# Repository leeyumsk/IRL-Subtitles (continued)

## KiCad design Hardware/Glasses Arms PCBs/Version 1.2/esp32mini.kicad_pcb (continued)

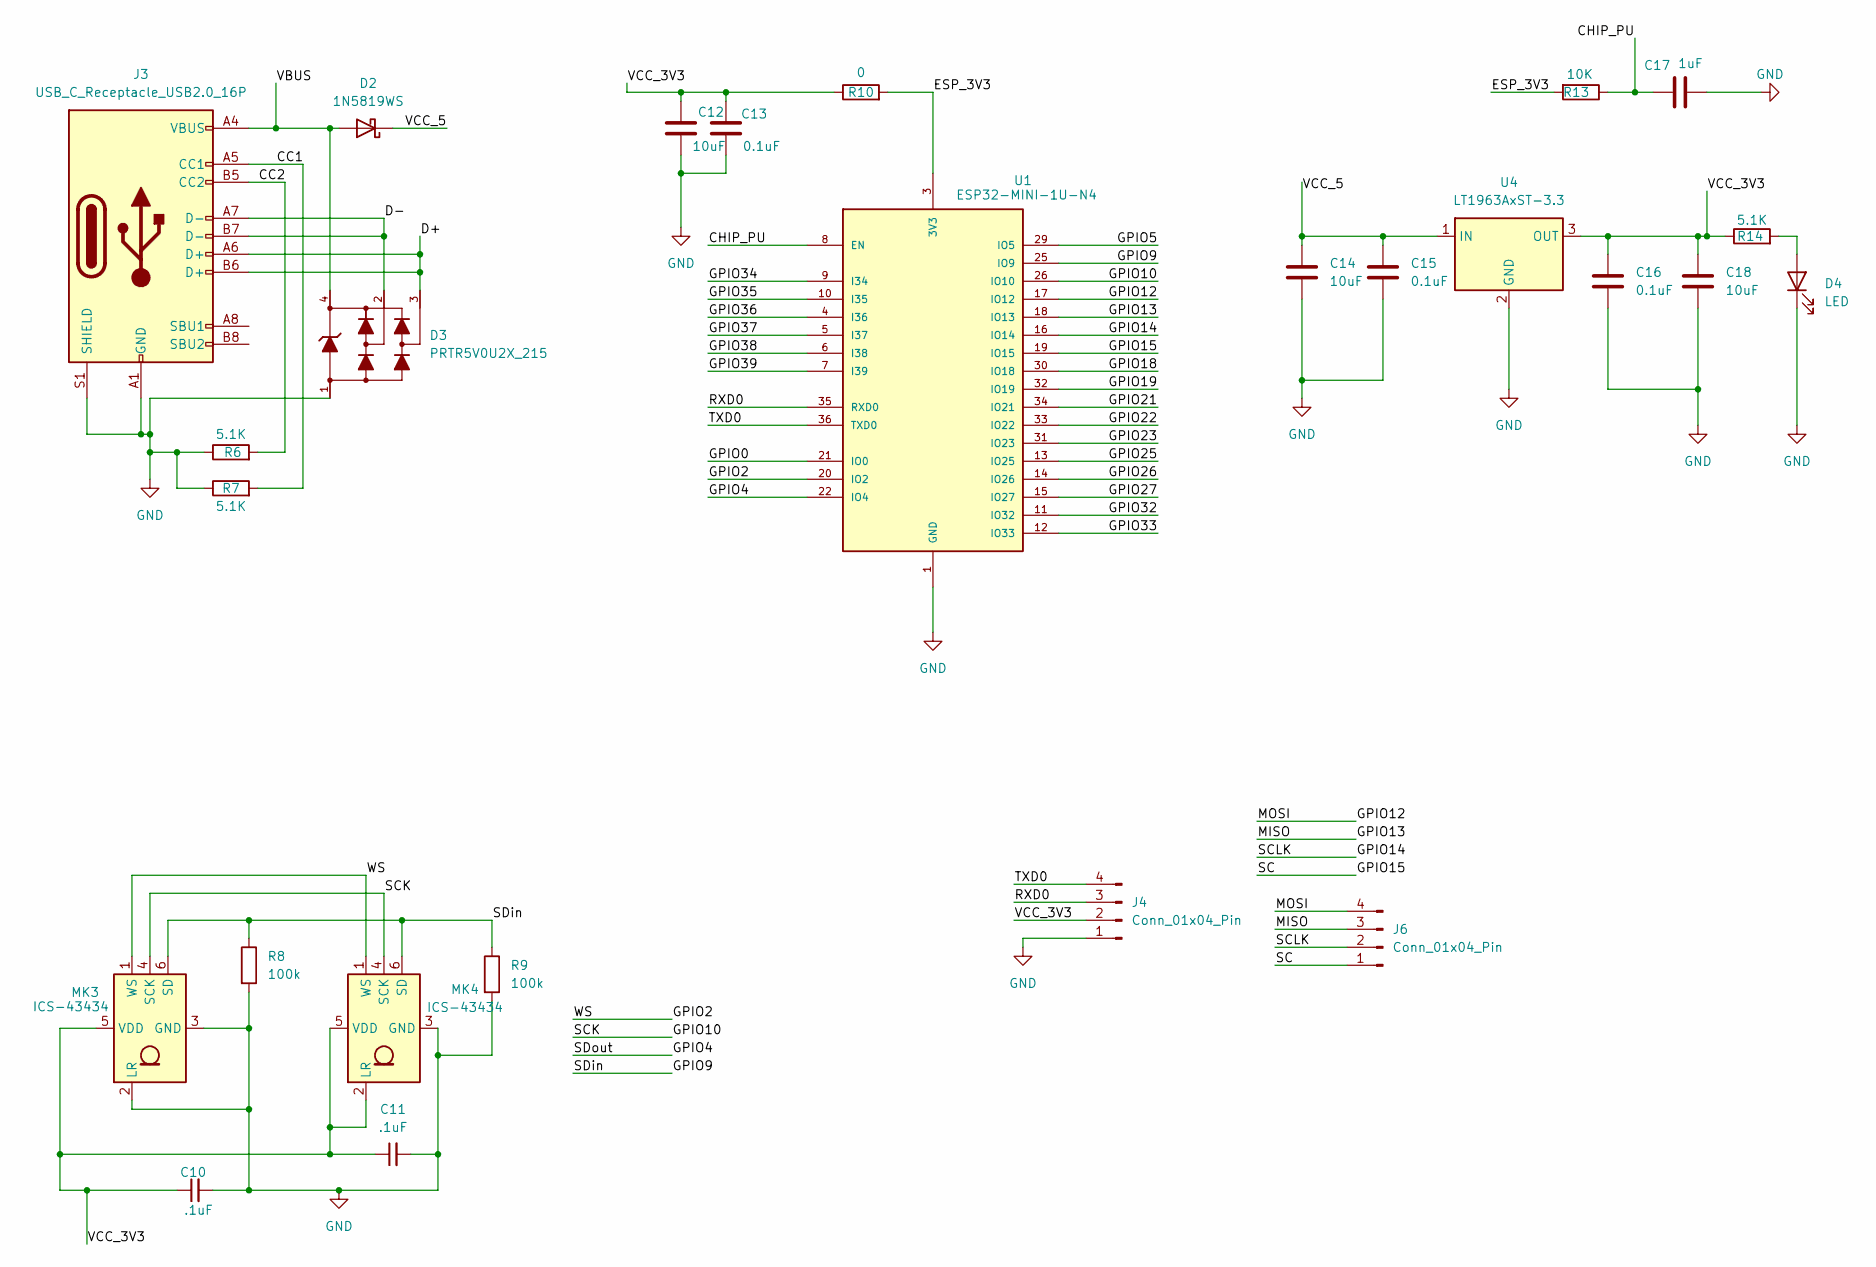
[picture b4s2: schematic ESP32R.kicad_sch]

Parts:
C10, C11: .1uF; C_0805_2012Metric_Pad1.18x1.45mm_HandSolder
C12, C14, C18: 10uF; C_0805_2012Metric_Pad1.18x1.45mm_HandSolder
C13, C15, C16: 0.1uF; C_0805_2012Metric_Pad1.18x1.45mm_HandSolder
C17: 1uF; C_0805_2012Metric_Pad1.18x1.45mm_HandSolder
D2: 1N5819WS; D_SOD-323
D3: PRTR5V0U2X_215; SOT143B
D4: LED; LED_0603_1608Metric_Pad1.05x0.95mm_HandSolder
J3: USB_C_Receptacle_USB2.0_16P; USB_C_Receptacle_JAE_DX07S016JA1R1500
J4, J6: Conn_01x04_Pin; PinHeader_1x04_P1.27mm_Vertical
MK3, MK4: ICS-43434; InvenSense_ICS-43434-6_3.5x2.65mm
R6, R7: 5.1K; R_0805_2012Metric_Pad1.20x1.40mm_HandSolder
R8, R9: 100k; R_0805_2012Metric_Pad1.20x1.40mm_HandSolder
R10: 0; SolderJumper-2_P1.3mm_Open_RoundedPad1.0x1.5mm
R13: 10K; R_0805_2012Metric
R14: 5.1K; R_0603_1608Metric_Pad0.98x0.95mm_HandSolder
U1: ESP32-MINI-1U-N4; MODULE_ESP32-MINI-1U-N4; PARTREV v1.2
U4: LT1963AxST-3.3; DCY0004A_N

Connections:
/BoardR/CC1: J3.A5 (CC1), R7.2
/BoardR/CC2: J3.B5 (CC2), R6.2
/BoardR/CHIP_PU: C17.1, R13.1, U1.8 (EN)
/BoardR/D+: D3.3, J3.A6 (D+), J3.B6 (D+)
/BoardR/D-: D3.2, J3.A7 (D-), J3.B7 (D-)
/BoardR/ESP_3V3: R10.2, R13.2, U1.3 (3V3)
/BoardR/GPIO0: U1.21 (IO0)
/BoardR/GPIO2: MK3.1 (WS), MK4.1 (WS), U1.20 (IO2)
/BoardR/GPIO4: U1.22 (IO4)
/BoardR/GPIO5: U1.29 (IO5)
/BoardR/GPIO9: MK3.6 (SD), MK4.6 (SD), R8.1, R9.1, U1.25 (IO9)
/BoardR/GPIO10: MK3.4 (SCK), MK4.4 (SCK), U1.26 (IO10)
/BoardR/GPIO12: J6.4, U1.17 (IO12)
/BoardR/GPIO13: J6.3, U1.18 (IO13)
/BoardR/GPIO14: J6.2, U1.16 (IO14)
/BoardR/GPIO15: J6.1, U1.19 (IO15)
/BoardR/GPIO18: U1.30 (IO18)
/BoardR/GPIO19: U1.32 (IO19)
/BoardR/GPIO21: U1.34 (IO21)
/BoardR/GPIO22: U1.33 (IO22)
/BoardR/GPIO23: U1.31 (IO23)
/BoardR/GPIO25: U1.13 (IO25)
/BoardR/GPIO26: U1.14 (IO26)
/BoardR/GPIO27: U1.15 (IO27)
/BoardR/GPIO32: U1.11 (IO32)
/BoardR/GPIO33: U1.12 (IO33)
/BoardR/GPIO34: U1.9 (I34)
/BoardR/GPIO35: U1.10 (I35)
/BoardR/GPIO36: U1.4 (I36)
/BoardR/GPIO37: U1.5 (I37)
/BoardR/GPIO38: U1.6 (I38)
/BoardR/GPIO39: U1.7 (I39)
/BoardR/RXD0: J4.3, U1.35 (RXD0)
/BoardR/TXD0: J4.4, U1.36 (TXD0)
/BoardR/VBUS: D2.2 (A), D3.4, J3.A4 (VBUS), J3.A9 (VBUS), J3.B4 (VBUS), J3.B9 (VBUS)
/BoardR/VCC_3V3: C10.1, C11.1, C12.1, C13.1, C16.1, C18.1, J4.2, MK3.5 (VDD), MK4.2 (LR), MK4.5 (VDD), R10.1, R14.1, U4.3 (OUT)
/BoardR/VCC_5: C14.1, C15.1, D2.1 (K), U4.1 (IN)
GND: C10.2, C11.2, C12.2, C13.2, C14.2, C15.2, C16.2, C17.2, C18.2, D3.1, D4.1 (K), J3.A1 (GND), J3.A12 (GND), J3.B1 (GND), J3.B12 (GND), J3.S1 (SHIELD), J4.1, MK3.2 (LR), MK3.3 (GND), MK4.3 (GND), R6.1, R7.1, R8.2, R9.2, U1.1 (GND), U1.2 (GND), U1.27 (GND), U1.38 (GND), U1.39 (GND), U1.40 (GND), U1.41 (GND), U1.42 (GND), U1.43 (GND), U1.44 (GND), U1.45 (GND), U1.46 (GND), U1.47 (GND), U1.48 (GND), U1.49 (GND), U1.50 (GND), U1.51 (GND), U1.52 (GND), U1.53 (GND), U1.54 (GND), U1.55 (GND), U1.56 (GND), U1.57 (GND), U1.58 (GND), U1.59 (GND), U1.60 (GND), U1.61 (GND), U1.62 (GND), U4.2 (GND); also elsewhere on the board
unnamed: D4.2 (A), R14.2

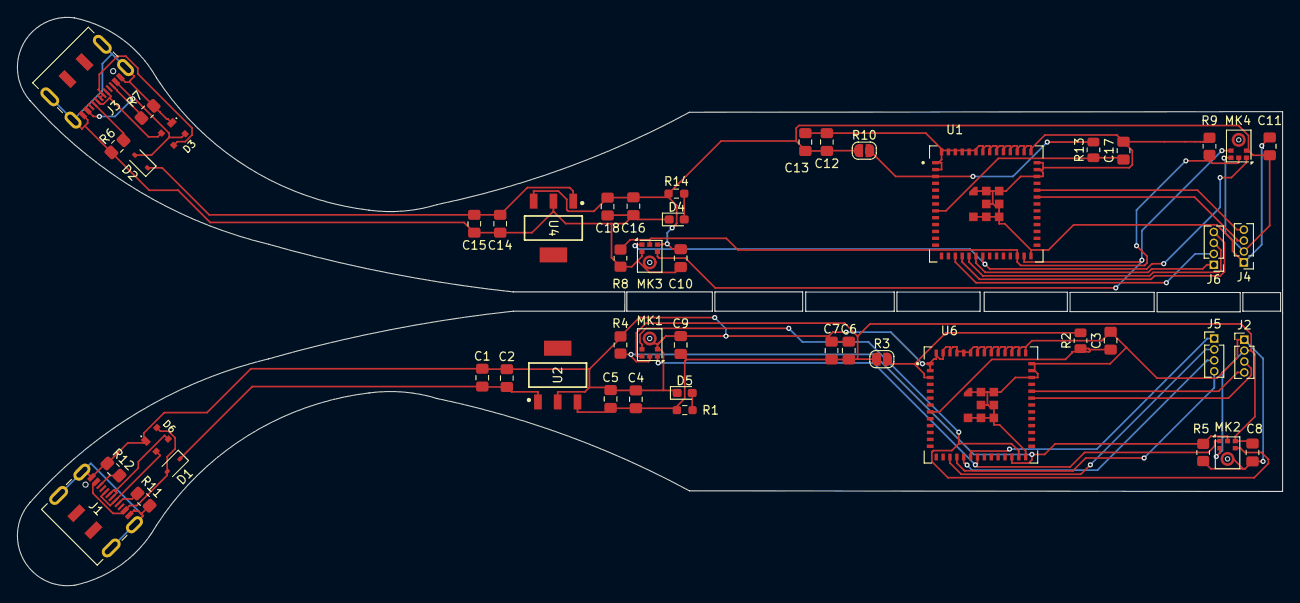
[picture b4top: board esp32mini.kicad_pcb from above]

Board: 2 copper layers, 147.1 x 66.1 mm, 52 parts (0 on the bottom side), 39 nets.

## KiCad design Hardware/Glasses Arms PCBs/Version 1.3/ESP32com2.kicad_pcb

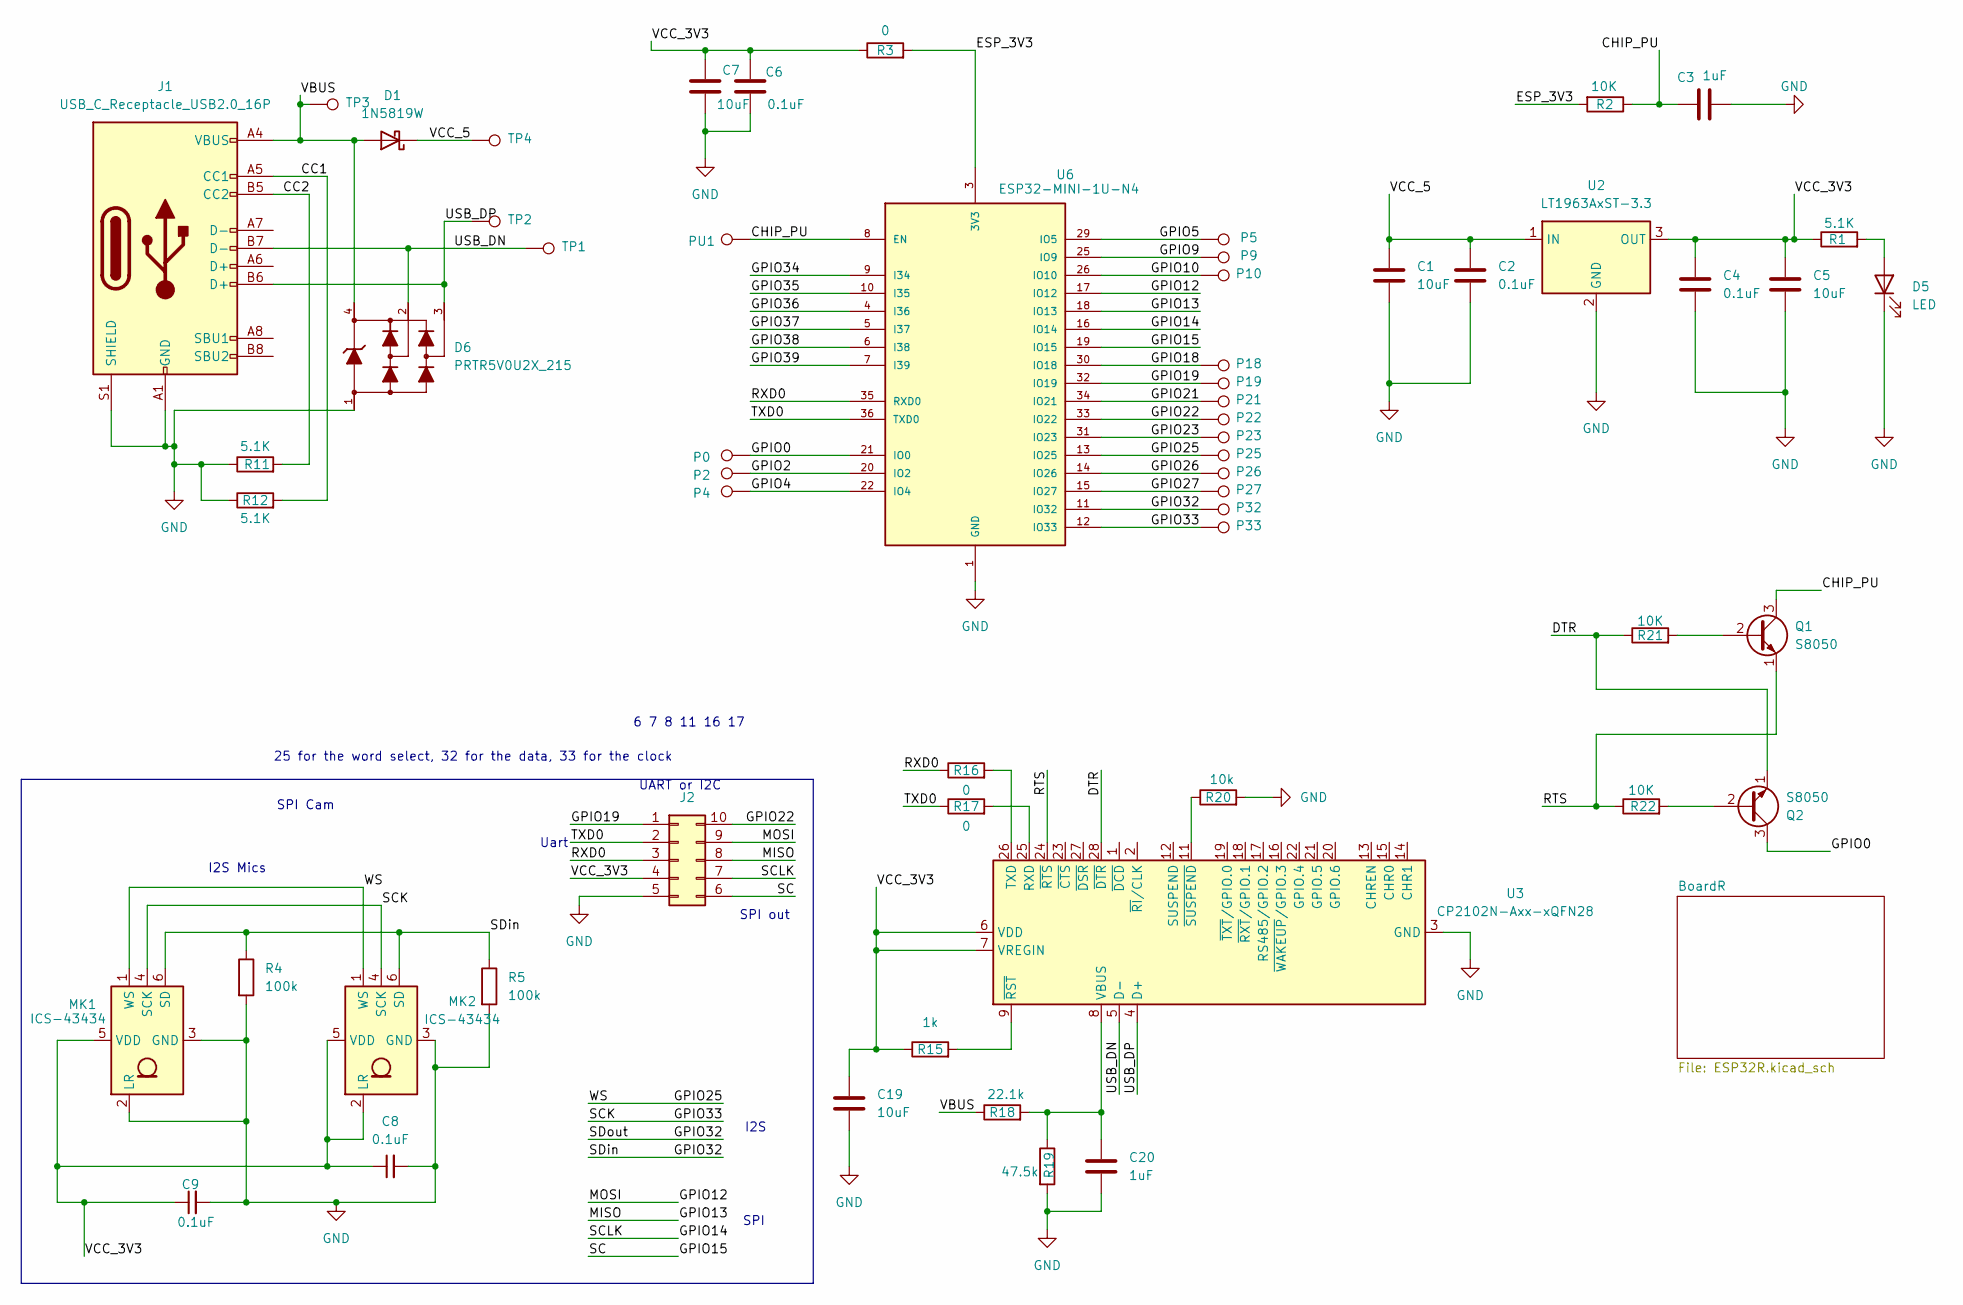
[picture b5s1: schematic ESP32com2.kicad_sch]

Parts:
C1, C5, C7, C19: 10uF; C_0805_2012Metric_Pad1.18x1.45mm_HandSolder
C2, C4, C6, C8, C9: 0.1uF; C_0805_2012Metric_Pad1.18x1.45mm_HandSolder
C3, C20: 1uF; C_0805_2012Metric_Pad1.18x1.45mm_HandSolder
D1: 1N5819W; D_SOD-123F
D5: LED; LED_0603_1608Metric_Pad1.05x0.95mm_HandSolder
D6: PRTR5V0U2X_215; SOT143B
J1: USB_C_Receptacle_USB2.0_16P; USB_C_Receptacle_JAE_DX07S016JA1R1500
J2: Conn_02x04_Counter_Clockwise; PinSocket_2x05_P2.00mm_Vertical
MK1, MK2: ICS-43434; InvenSense_ICS-43434-6_3.5x2.65mm
P0, P2, P4, P5, P9, P10, P18, P19, P21, P22, P23, P25, P26, P27, P32, P33: TestPoint; TestPoint_Pad_1.0x1.0mm
PU1: TestPoint; TestPoint_Pad_1.0x1.0mm
Q1, Q2: S8050; SOT-23-3
R1: 5.1K; R_0603_1608Metric_Pad0.98x0.95mm_HandSolder
R2: 10K; R_0805_2012Metric
R3: 0; SolderJumper-2_P1.3mm_Open_RoundedPad1.0x1.5mm
R4, R5: 100k; R_0805_2012Metric_Pad1.20x1.40mm_HandSolder
R11, R12: 5.1K; R_0805_2012Metric_Pad1.20x1.40mm_HandSolder
R15: 1k; R_0805_2012Metric_Pad1.20x1.40mm_HandSolder
R16, R17: 0; SolderJumper-2_P1.3mm_Bridged_RoundedPad1.0x1.5mm
R18: 22.1k; R_0805_2012Metric_Pad1.20x1.40mm_HandSolder
R19: 47.5k; R_0805_2012Metric_Pad1.20x1.40mm_HandSolder
R20: 10k; R_0805_2012Metric_Pad1.20x1.40mm_HandSolder
R21, R22: 10K; R_0805_2012Metric_Pad1.20x1.40mm_HandSolder
TP1, TP2, TP3, TP4: TestPoint; TestPoint_Pad_1.0x1.0mm
U2: LT1963AxST-3.3; SOT-223-3_TabPin2
U3: CP2102N-Axx-xQFN28; QFN-28-1EP_5x5mm_P0.5mm_EP3.35x3.35mm
U6: ESP32-MINI-1U-N4; MODULE_ESP32-MINI-1U-N4; PARTREV v1.2

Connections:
/CC1: J1.A5 (CC1), R12.2
/CC2: J1.B5 (CC2), R11.2
/CHIP_PU: C3.1, PU1.1, Q1.3 (C), R2.1, U6.8 (EN)
/DTR: Q2.1 (E), R21.1, U3.28 (~DTR)
/ESP_3V3: R2.2, R3.2, U6.3 (3V3)
/GPIO0: P0.1, Q2.3 (C), U6.21 (IO0)
/GPIO2: P2.1, U6.20 (IO2)
/GPIO4: P4.1, U6.22 (IO4)
/GPIO5: P5.1, U6.29 (IO5)
/GPIO9: P9.1, U6.25 (IO9)
/GPIO10: P10.1, U6.26 (IO10)
/GPIO12: J2.9, U6.17 (IO12)
/GPIO13: J2.8, U6.18 (IO13)
/GPIO14: J2.7, U6.16 (IO14)
/GPIO15: J2.6, U6.19 (IO15)
/GPIO18: P18.1, U6.30 (IO18)
/GPIO19: J2.1, P19.1, U6.32 (IO19)
/GPIO21: P21.1, U6.34 (IO21)
/GPIO22: J2.10, P22.1, U6.33 (IO22)
/GPIO23: P23.1, U6.31 (IO23)
/GPIO25: MK1.1 (WS), MK2.1 (WS), P25.1, U6.13 (IO25)
/GPIO26: P26.1, U6.14 (IO26)
/GPIO27: P27.1, U6.15 (IO27)
/GPIO32: MK1.6 (SD), MK2.6 (SD), P32.1, R4.1, R5.1, U6.11 (IO32)
/GPIO33: MK1.4 (SCK), MK2.4 (SCK), P33.1, U6.12 (IO33)
/GPIO34: U6.9 (I34)
/GPIO35: U6.10 (I35)
/GPIO36: U6.4 (I36)
/GPIO37: U6.5 (I37)
/GPIO38: U6.6 (I38)
/GPIO39: U6.7 (I39)
/RTS: Q1.1 (E), R22.1, U3.24 (~RTS)
/RXD0: J2.3, R16.1, U6.35 (RXD0)
/TXD0: J2.2, R17.1, U6.36 (TXD0)
/USB_DN: D6.2, J1.B7 (D-), TP1.1, U3.5 (D-)
/USB_DP: D6.3, J1.B6 (D+), TP2.1, U3.4 (D+)
/VBUS: D1.2 (A), D6.4, J1.A4 (VBUS), J1.A9 (VBUS), J1.B4 (VBUS), J1.B9 (VBUS), R18.1, TP3.1
/VCC_3V3: C4.1, C5.1, C6.1, C7.1, C8.1, C9.1, C19.1, J2.4, MK1.5 (VDD), MK2.2 (LR), MK2.5 (VDD), R1.1, R3.1, R15.1, U2.3 (OUT), U3.6 (VDD), U3.7 (VREGIN)
/VCC_5: C1.1, C2.1, D1.1 (K), TP4.1, U2.1 (IN)
GND: C1.2, C2.2, C3.2, C4.2, C5.2, C6.2, C7.2, C8.2, C9.2, C19.2, C20.2, D5.1 (K), D6.1, J1.A1 (GND), J1.A12 (GND), J1.B1 (GND), J1.B12 (GND), J1.S1 (SHIELD), J2.5, MK1.2 (LR), MK1.3 (GND), MK2.3 (GND), R4.2, R5.2, R11.1, R12.1, R19.2, R20.2, U2.2 (GND), U2.4 (GND), U3.3 (GND), U3.29 (GND), U6.1 (GND), U6.2 (GND), U6.27 (GND), U6.38 (GND), U6.39 (GND), U6.40 (GND), U6.41 (GND), U6.42 (GND), U6.43 (GND), U6.44 (GND), U6.45 (GND), U6.46 (GND), U6.47 (GND), U6.48 (GND), U6.49 (GND), U6.50 (GND), U6.51 (GND), U6.52 (GND), U6.53 (GND), U6.54 (GND), U6.55 (GND), U6.56 (GND), U6.57 (GND), U6.58 (GND), U6.59 (GND), U6.60 (GND), U6.61 (GND), U6.62 (GND); also elsewhere on the board
unnamed: D5.2 (A), R1.2
unnamed: Q1.2 (B), R21.2
unnamed: Q2.2 (B), R22.2
unnamed: R17.2, U3.25 (RXD)
unnamed: R16.2, U3.26 (TXD)
unnamed: C20.1, R18.2, R19.1, U3.8 (VBUS)
unnamed: R15.2, U3.9 (~RST)
unnamed: R20.1, U3.11 (~SUSPEND)

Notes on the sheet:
UART or I2C
I2S
SPI Cam
25 for the word select, 32 for the data, 33 for the clock
I2S Mics
Uart
SPI out
6 7 8 11 16 17
SPI

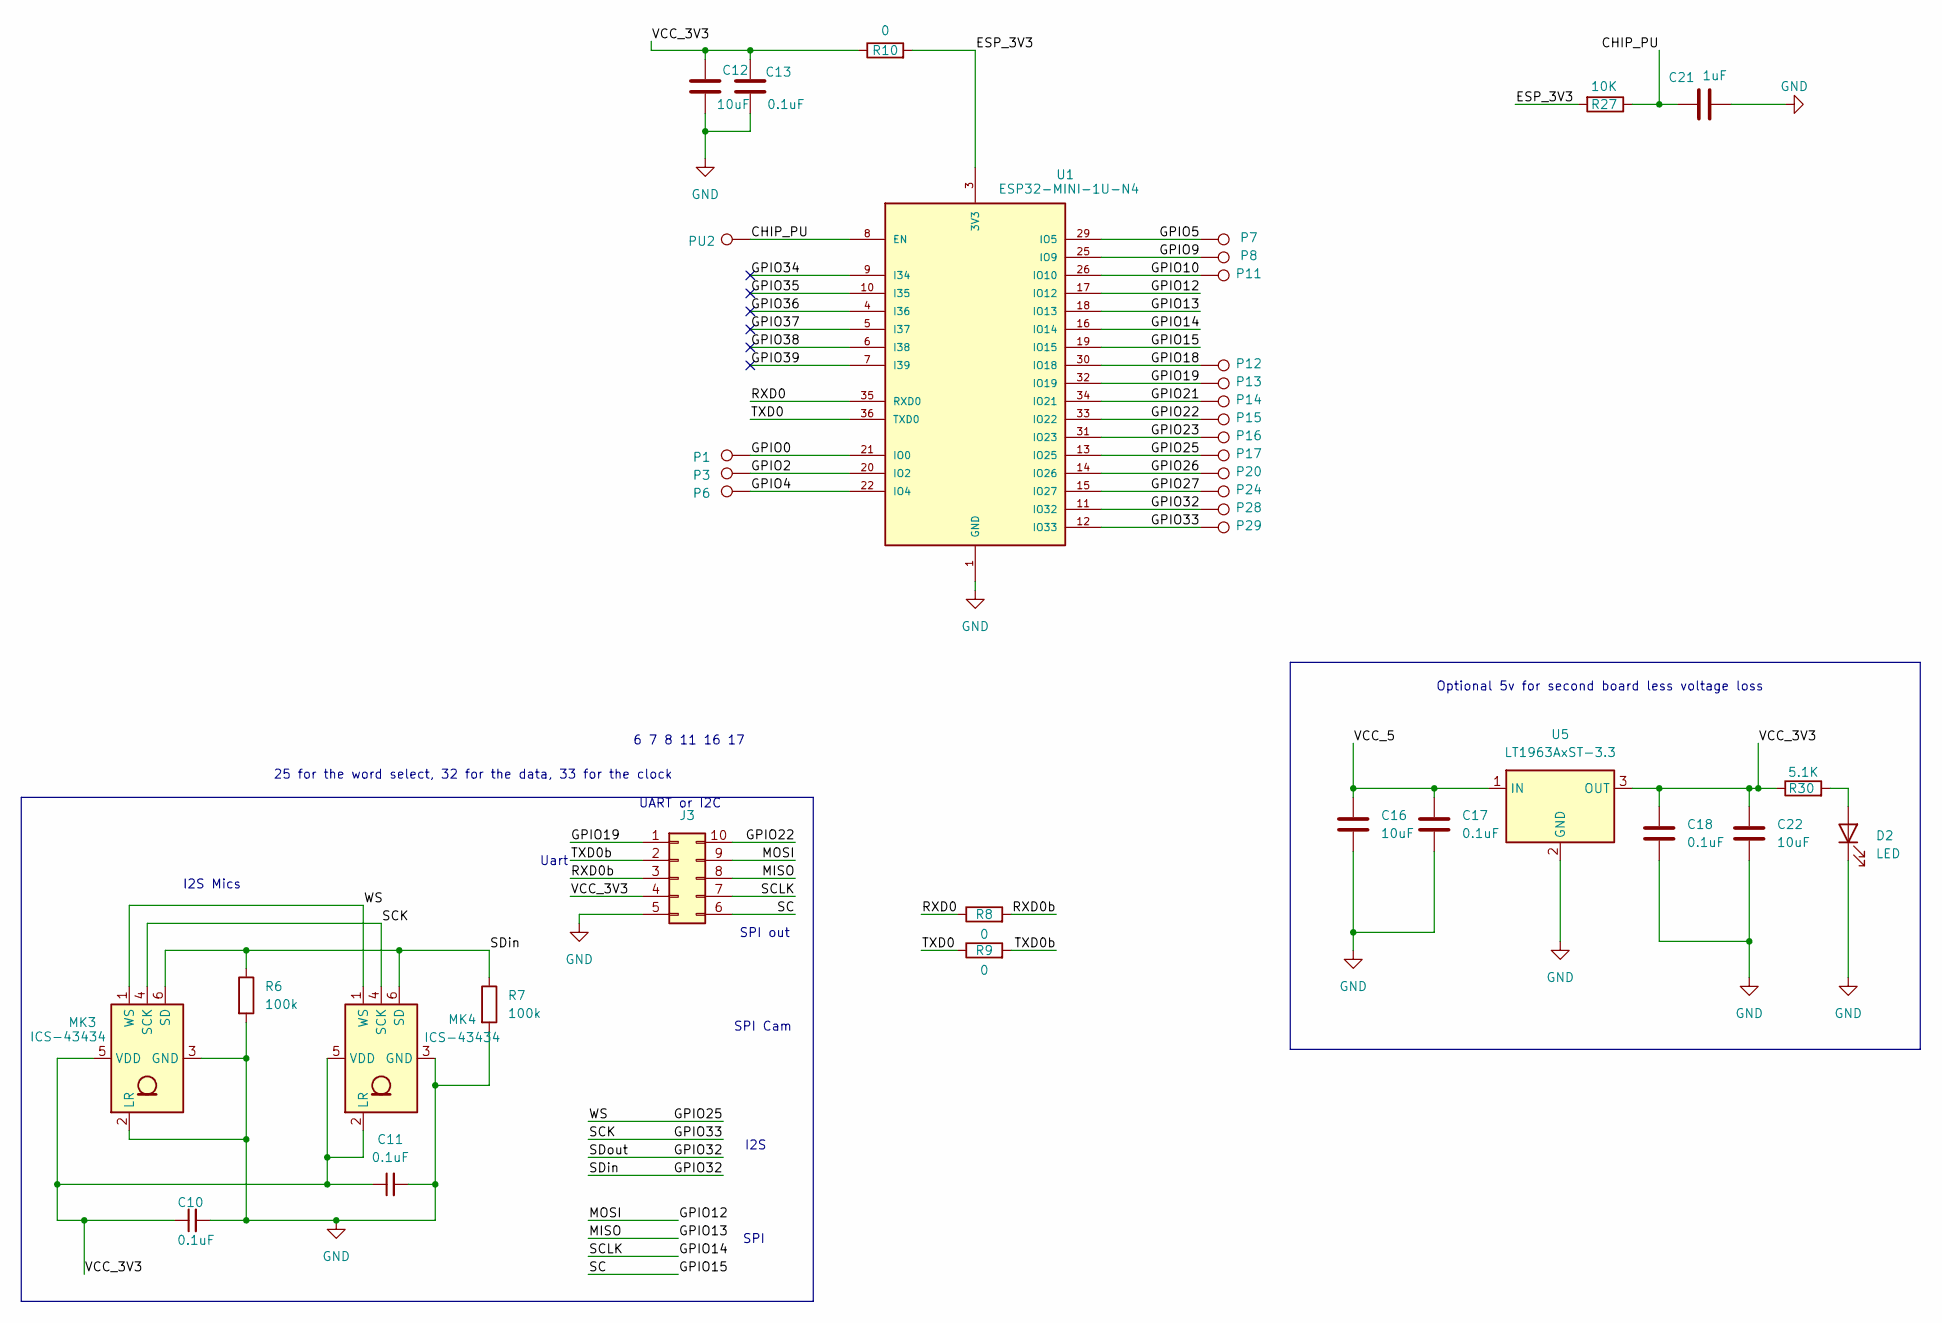
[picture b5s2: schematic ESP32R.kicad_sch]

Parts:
C10, C11, C13, C17, C18: 0.1uF; C_0805_2012Metric_Pad1.18x1.45mm_HandSolder
C12, C16, C22: 10uF; C_0805_2012Metric_Pad1.18x1.45mm_HandSolder
C21: 1uF; C_0805_2012Metric_Pad1.18x1.45mm_HandSolder
D2: LED; LED_0603_1608Metric_Pad1.05x0.95mm_HandSolder
J3: Conn_02x04_Counter_Clockwise; PinSocket_2x05_P2.00mm_Vertical
MK3, MK4: ICS-43434; InvenSense_ICS-43434-6_3.5x2.65mm
P1, P3, P6, P7, P8, P11, P12, P13, P14, P15, P16, P17, P20, P24, P28, P29: TestPoint; TestPoint_Pad_1.0x1.0mm
PU2: TestPoint; TestPoint_Pad_1.0x1.0mm
R6, R7: 100k; R_0805_2012Metric_Pad1.20x1.40mm_HandSolder
R8, R9: 0; SolderJumper-2_P1.3mm_Bridged_RoundedPad1.0x1.5mm
R10: 0; SolderJumper-2_P1.3mm_Open_RoundedPad1.0x1.5mm
R27: 10K; R_0805_2012Metric
R30: 5.1K; R_0603_1608Metric_Pad0.98x0.95mm_HandSolder
U1: ESP32-MINI-1U-N4; MODULE_ESP32-MINI-1U-N4; PARTREV v1.2
U5: LT1963AxST-3.3; SOT-223-3_TabPin2

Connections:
/BoardR/CHIP_PU: C21.1, PU2.1, R27.1, U1.8 (EN)
/BoardR/ESP_3V3: R10.2, R27.2, U1.3 (3V3)
/BoardR/GPIO0: P1.1, U1.21 (IO0)
/BoardR/GPIO2: P3.1, U1.20 (IO2)
/BoardR/GPIO4: P6.1, U1.22 (IO4)
/BoardR/GPIO5: P7.1, U1.29 (IO5)
/BoardR/GPIO9: P8.1, U1.25 (IO9)
/BoardR/GPIO10: P11.1, U1.26 (IO10)
/BoardR/GPIO12: J3.9, U1.17 (IO12)
/BoardR/GPIO13: J3.8, U1.18 (IO13)
/BoardR/GPIO14: J3.7, U1.16 (IO14)
/BoardR/GPIO15: J3.6, U1.19 (IO15)
/BoardR/GPIO18: P12.1, U1.30 (IO18)
/BoardR/GPIO19: J3.1, P13.1, U1.32 (IO19)
/BoardR/GPIO21: P14.1, U1.34 (IO21)
/BoardR/GPIO22: J3.10, P15.1, U1.33 (IO22)
/BoardR/GPIO23: P16.1, U1.31 (IO23)
/BoardR/GPIO25: MK3.1 (WS), MK4.1 (WS), P17.1, U1.13 (IO25)
/BoardR/GPIO26: P20.1, U1.14 (IO26)
/BoardR/GPIO27: P24.1, U1.15 (IO27)
/BoardR/GPIO32: MK3.6 (SD), MK4.6 (SD), P28.1, R6.1, R7.1, U1.11 (IO32)
/BoardR/GPIO33: MK3.4 (SCK), MK4.4 (SCK), P29.1, U1.12 (IO33)
/BoardR/GPIO34: U1.9 (I34)
/BoardR/GPIO35: U1.10 (I35)
/BoardR/GPIO36: U1.4 (I36)
/BoardR/GPIO37: U1.5 (I37)
/BoardR/GPIO38: U1.6 (I38)
/BoardR/GPIO39: U1.7 (I39)
/BoardR/RXD0: R8.1, U1.35 (RXD0)
/BoardR/RXD0b: J3.3, R8.2
/BoardR/TXD0: R9.1, U1.36 (TXD0)
/BoardR/TXD0b: J3.2, R9.2
/BoardR/VCC_3V3: C10.1, C11.1, C12.1, C13.1, C18.1, C22.1, J3.4, MK3.5 (VDD), MK4.2 (LR), MK4.5 (VDD), R10.1, R30.1, U5.3 (OUT)
GND: C10.2, C11.2, C12.2, C13.2, C16.2, C17.2, C18.2, C21.2, C22.2, D2.1 (K), J3.5, MK3.2 (LR), MK3.3 (GND), MK4.3 (GND), R6.2, R7.2, U1.1 (GND), U1.2 (GND), U1.27 (GND), U1.38 (GND), U1.39 (GND), U1.40 (GND), U1.41 (GND), U1.42 (GND), U1.43 (GND), U1.44 (GND), U1.45 (GND), U1.46 (GND), U1.47 (GND), U1.48 (GND), U1.49 (GND), U1.50 (GND), U1.51 (GND), U1.52 (GND), U1.53 (GND), U1.54 (GND), U1.55 (GND), U1.56 (GND), U1.57 (GND), U1.58 (GND), U1.59 (GND), U1.60 (GND), U1.61 (GND), U1.62 (GND), U5.2 (GND), U5.4 (GND); also elsewhere on the board
unnamed: C16.1, C17.1, U5.1 (IN)
unnamed: D2.2 (A), R30.2

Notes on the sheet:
Uart
SPI out
SPI Cam
UART or I2C
Optional 5v for second board less voltage loss
I2S Mics
25 for the word select, 32 for the data, 33 for the clock
SPI
I2S
6 7 8 11 16 17

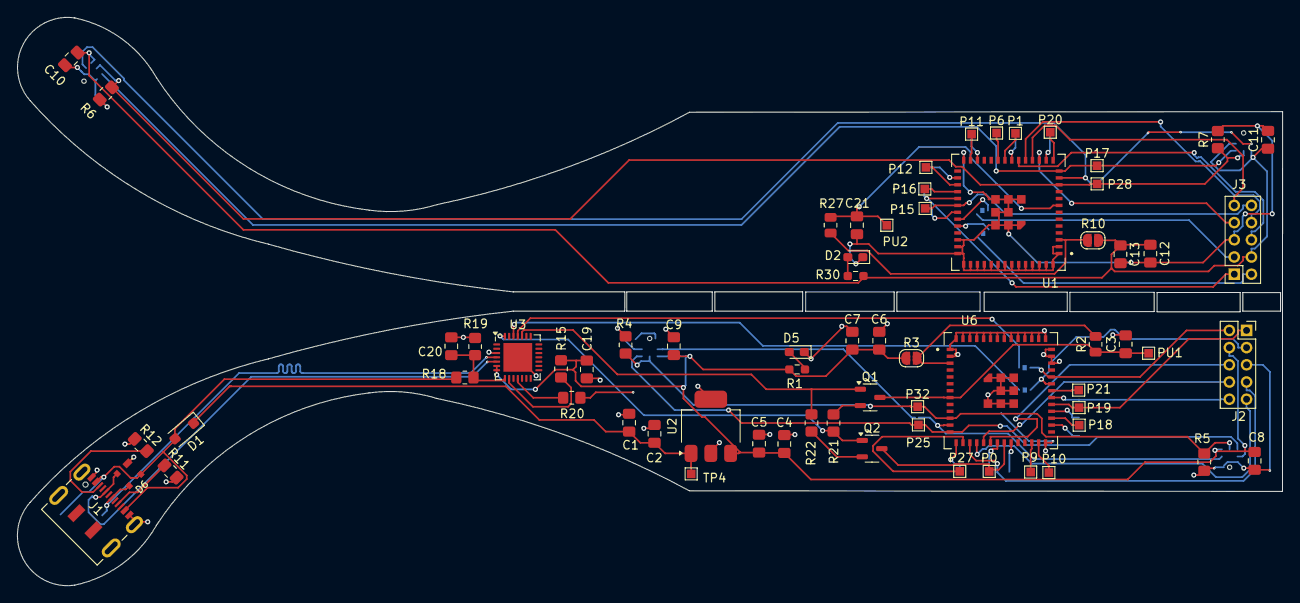
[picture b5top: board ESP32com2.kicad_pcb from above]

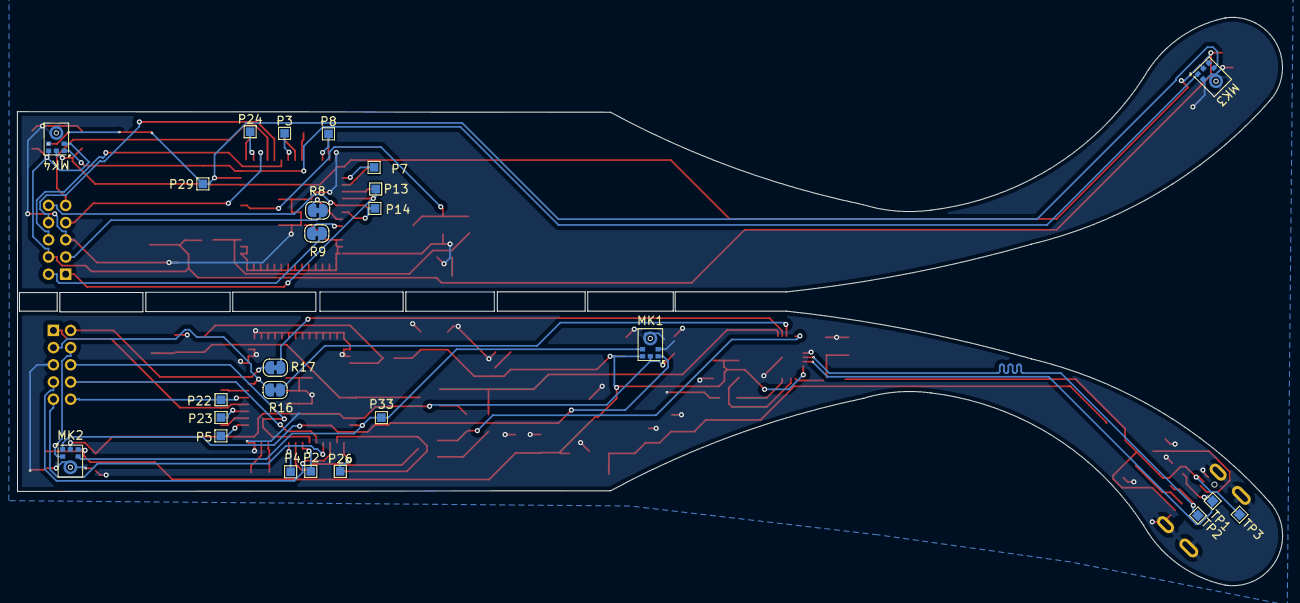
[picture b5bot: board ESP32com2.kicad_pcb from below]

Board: 2 copper layers, 147.1 x 66.1 mm, 93 parts (25 on the bottom side), 70 nets.

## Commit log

2024-10-01 Test commit
2024-10-02 Create ESP-IDF Project
2024-11-05 Facial Detection Code for the IRL Subtitles Projects
    This section of the code deals with detection faces, speech and places boxes for where the subtitles will be placed on the screen
2024-11-06 The current implementation returns 1 image from the camera per ping to <ip>/stream
2024-11-07 This commit contains changes to softap_example_main.c's
    stream_handler() function, which now supports transmitting
    live video over Wi-Fi.
    Also added a .gitignore which excludes build folders and
    a few other files created at build time.
2024-11-07 This commit adds the <ip>/ach1 URI to connect to the ESP32's bitstream for audio channel 1.
    If you connect to it on the browser, it will just start downloading byte data into your downloads folder.
    You can use playAudioFromESP32v7.py instead.
    It will continue reading from <ip>/ach1 until the user presses Ctrl+C to interrupt the program
    Then it prints some info and saves the audio as a .wav file.
2024-11-09 Audio and Video capture(untested)
    untested audio and video capturing code
2024-11-09 Face detection and video capture combined
2024-11-13 Face, Video scrape, Audio scrape, subtitles
    This is the current Facedetection3.0 code which implements the video scraping into the OpenCV display. the audio scraping is used in unison with this to display the subtitles as well. And the whisper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
2024-11-14 updated file structure
2024-11-14 added placeholeders to folders and stated extra doc readme.md
2024-11-14 edit to readme in ex doc
2024-11-14 edit to table in read me
2024-11-14 test
2024-11-14 fixed table
2024-11-14 fixed
2024-11-14 added adio test methods file
2024-11-14 edit
2024-11-14 added
2024-11-14 edit file structure
2024-11-15 deleted
2025-01-24 added version 3 for the board
2025-01-24 adds component specs
2025-01-29 Version 3.1
2025-02-03 add PCB Versions
2025-02-12 update and add
2025-02-12 updat
2025-02-12 Update FaceDetection.py
    Edited FaceDetection.py, added diagnostic code that tells you where haarcascade_mcs_mouth.xml should be placed
2025-02-13 added component docs
2025-02-19 production files added
2025-03-21 added place holders
2025-03-22 Code for testing the face detection with the mics
    The codes will use the face detection and the mics to locate where the speaker is
2025-03-28 start of ODAS config
2025-03-28 running test
2025-03-30 updated configuration
2025-04-03 config and tests
2025-04-03 run files
2025-04-03 change location
2025-04-13 arm board firmware
2025-04-13 made easier to configure
2025-04-13 moved to folder
2025-04-13 slimming
2025-04-13 added pin layout
2025-04-13 edit table
2025-04-13 spelling
2025-04-13 added trouble shooting step
2025-04-13 test code for localization
2025-04-13 working 2d localization
2025-04-13 localization attemps
2025-04-13 add more localization stuff
2025-04-13 added attempted solution
2025-04-14 moved to be closer file format
2025-04-14 Squashed commit of the following:
    commit cd66e0a1305f8fe2782743b6b9fd62e6e4d255bb
    Author: Koalaven <102919896+Koalaven@users.noreply.github.com>
    Date: Mon Apr 14 14:12:40 2025 -0400
    moved to be closer file format
    commit 58886cd4b8a11e447f16aa333d6f8a5f13fe3d6a
    Author: leeyumsk <123519050+leeyumsk@users.noreply.github.com>
2025-04-14 added cad models
    frames
2025-04-14 assembly picture
2025-04-14 Rename Screenshot 2025-04-14 152832.png to assemblypic.png
2025-04-14 Update README.md
    frames
2025-04-15 Revert "moved to folder"
    This reverts commit fb777bde0258e95557f338e6bfeef77cc45969e7.
2025-04-15 add code from other branches
2025-04-23 Moved to folder to smoothy merge
2025-04-23 Added README back
